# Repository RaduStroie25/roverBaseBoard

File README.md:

# roverBaseBoard
My Rover Project, too lazy to write another description. View documentation in the files. :P
STATUS: Unfinished

### Board Pins (Input)
These are the board pins that take input from the Microcontroller:
- 8x Digital pins. (for all motor driver direction control)
- 4x PWM or Analog pins. (for all motor speed control)
- 1x VCC pin (for driver logic voltage that can be 2.5V-5.5V)
- 1x Digital pin. (for driver Standby pins)
- 1x POWERLATCH pin (keep high while running)

### Board Pins (Output)
These are the pins that the board offers to a microcontroller:
- 1x Adjustable VCC power pin.
- 1x GND into the same source.
- 1x SCL (ina219)
- 1x SDA (ina219)

## Notes
- Measured TT motor max draw per motor 110mA-120mA. (without load or wheels on)
- do not run 75A through jumper cables... *

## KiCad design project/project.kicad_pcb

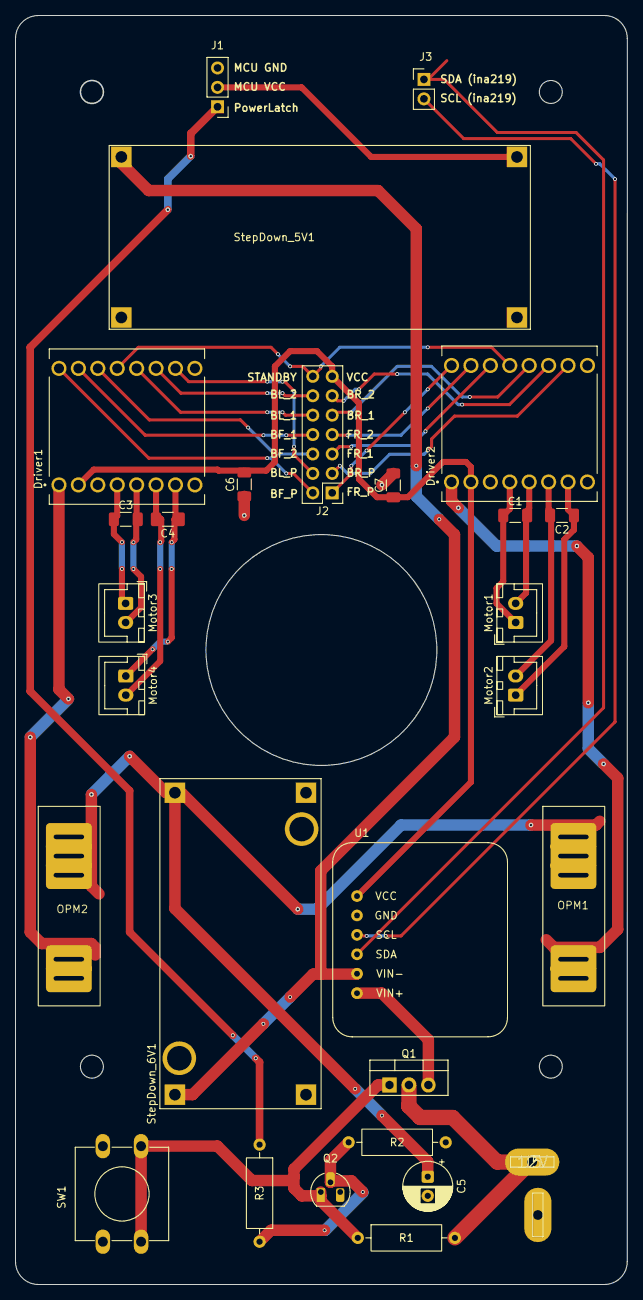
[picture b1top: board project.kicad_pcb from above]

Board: 2 copper layers, 80.0 x 166.0 mm, 28 parts (0 on the bottom side), 35 nets.

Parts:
C1, C2, C3, C4, C6, C7: 100nF; C_1206_3216Metric_Pad1.33x1.80mm_HandSolder
C5: 100uF; CP_Radial_D6.3mm_P2.50mm
Driver1, Driver2: ROB-14450; MODULE_ROB-14450
J1: Conn_01x03; PinHeader_1x03_P2.54mm_Vertical
J2: Conn_02x07_Odd_Even; PinHeader_2x07_P2.54mm_Vertical
J3: Conn_01x02; PinHeader_1x02_P2.54mm_Vertical
J5: 12V; DEANS
Motor1, Motor2, Motor3, Motor4: Conn_01x02_Pin; JST_XH_B2B-XH-A_1x02_P2.50mm_Vertical
OPM1, OPM2: 1A; OPM_Kuoyuh_91
Q1: IRF4905; TO-220-3_Vertical
Q2: NPN; TO-92_HandSolder
R1, R2: 10k; R_Axial_DIN0309_L9.0mm_D3.2mm_P12.70mm_Horizontal
R3: 4.7k; R_Axial_DIN0309_L9.0mm_D3.2mm_P12.70mm_Horizontal
SW1: SW_Push; SW_PUSH-12mm
StepDown_5V1: XL4015_Module; XL4015_StepDown_Module
StepDown_6V1: LM2596_Module; CONV_MC00100
U1: module_ina219

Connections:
/PowLatch: J1.1, R3.1
/STANDBY: Driver1.13 (STBY), Driver2.13 (STBY), J2.14
/VCC: C6.2, C7.1, Driver1.2 (VCC), Driver2.2 (VCC), J2.13, U1.1 (VCC)
/VM: C5.1, OPM1.2 (B), OPM2.2 (B), StepDown_6V1.OUT+
GND: C5.2, C6.1, C7.2, Driver1.3 (GND), Driver1.8 (GND), Driver1.9 (GND), Driver2.3 (GND), Driver2.8 (GND), Driver2.9 (GND), J1.3, J5.- (Pin_2), Q2.3 (E), R2.1, SW1.1, StepDown_5V1.IN-, StepDown_5V1.OUT-, StepDown_6V1.IN-, StepDown_6V1.OUT-, U1.2 (GND)
unnamed: C3.1, Driver1.4 (A01), Motor3.1
unnamed: C3.2, Driver1.5 (A02), Motor3.2
unnamed: Driver1.14 (AI1), J2.6
unnamed: Driver1.15 (AI2), J2.8
unnamed: C4.1, Driver1.7 (B01), Motor4.1
unnamed: C4.2, Driver1.6 (B02), Motor4.2
unnamed: Driver1.12 (BI1), J2.10
unnamed: Driver1.11 (BI2), J2.12
unnamed: Driver1.16 (PWMA), J2.2
unnamed: Driver1.10 (PWMB), J2.4
unnamed: Driver1.1 (VM), OPM2.1 (A)
unnamed: C1.1, Driver2.4 (A01), Motor1.1
unnamed: C1.2, Driver2.5 (A02), Motor1.2
unnamed: Driver2.14 (AI1), J2.5
unnamed: Driver2.15 (AI2), J2.7
unnamed: C2.1, Driver2.7 (B01), Motor2.1
unnamed: C2.2, Driver2.6 (B02), Motor2.2
unnamed: Driver2.12 (BI1), J2.9
unnamed: Driver2.11 (BI2), J2.11
unnamed: Driver2.16 (PWMA), J2.1
unnamed: Driver2.10 (PWMB), J2.3
unnamed: Driver2.1 (VM), OPM1.1 (A)
unnamed: J1.2, StepDown_5V1.OUT+
unnamed: J3.1, U1.4 (SDA)
unnamed: J3.2, U1.3 (SCL)
unnamed: J5.+ (Pin_1), Q1.2 (D), R1.2
unnamed: Q1.1 (G), Q2.1 (C), R1.1, SW1.2
unnamed: Q1.3 (S), U1.6 (VIN+)
unnamed: Q2.2 (B), R2.2, R3.2
unnamed: StepDown_5V1.IN+, StepDown_6V1.IN+, U1.5 (VIN-)
